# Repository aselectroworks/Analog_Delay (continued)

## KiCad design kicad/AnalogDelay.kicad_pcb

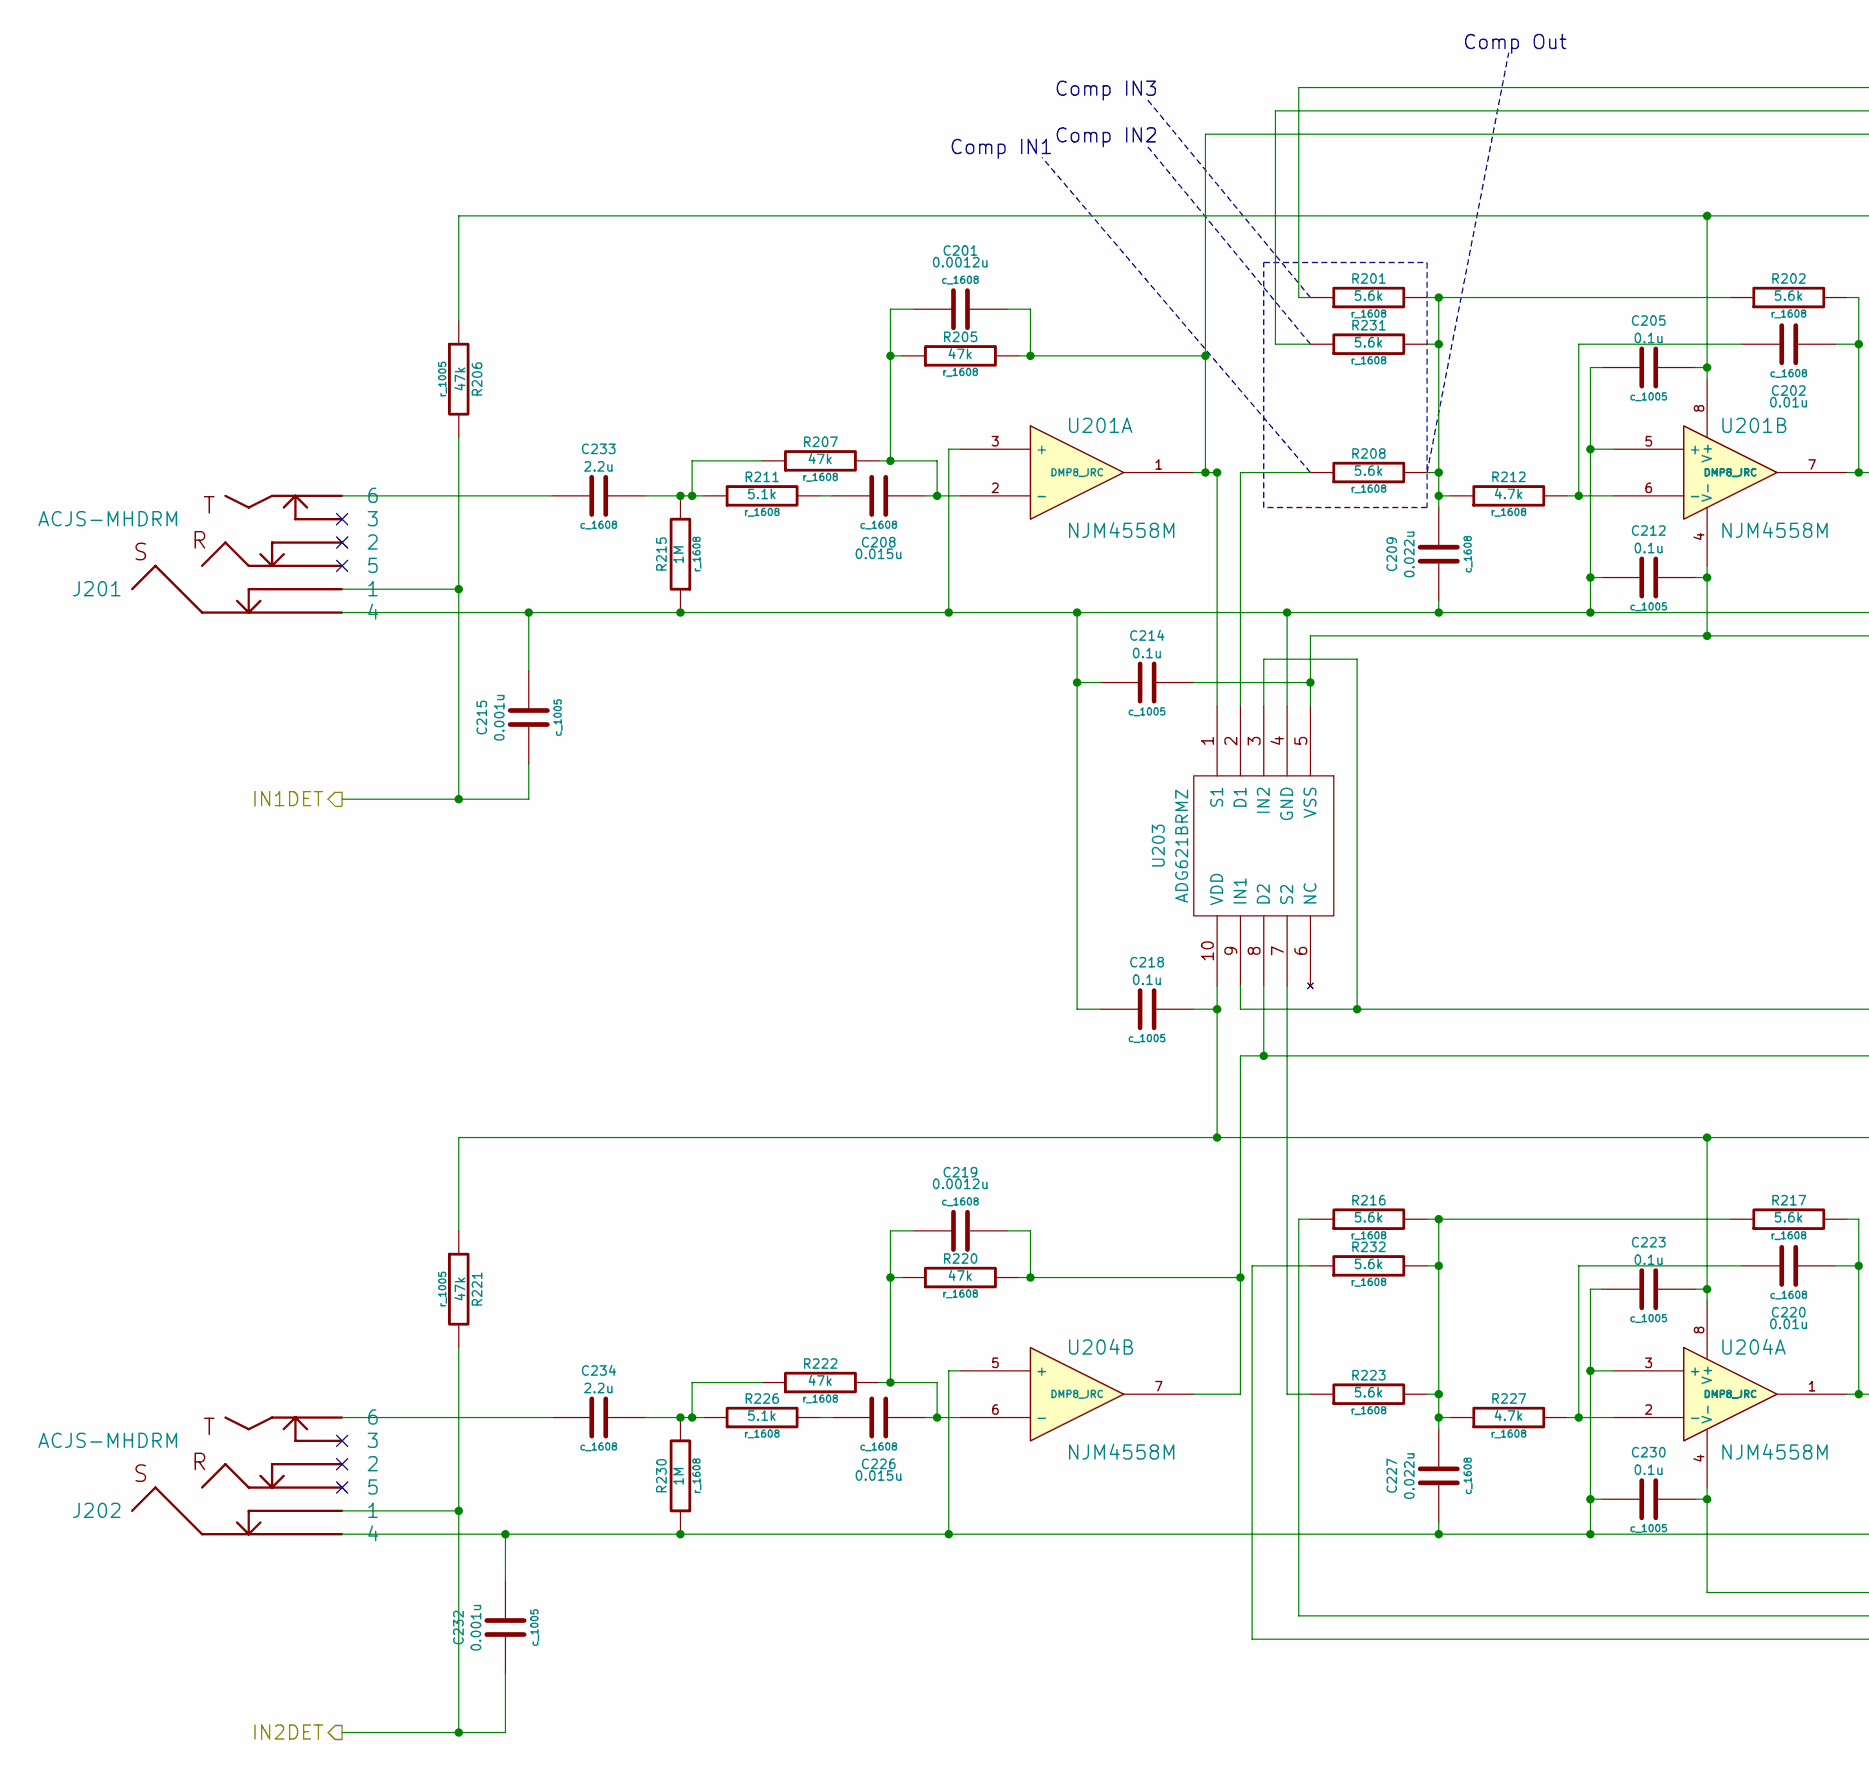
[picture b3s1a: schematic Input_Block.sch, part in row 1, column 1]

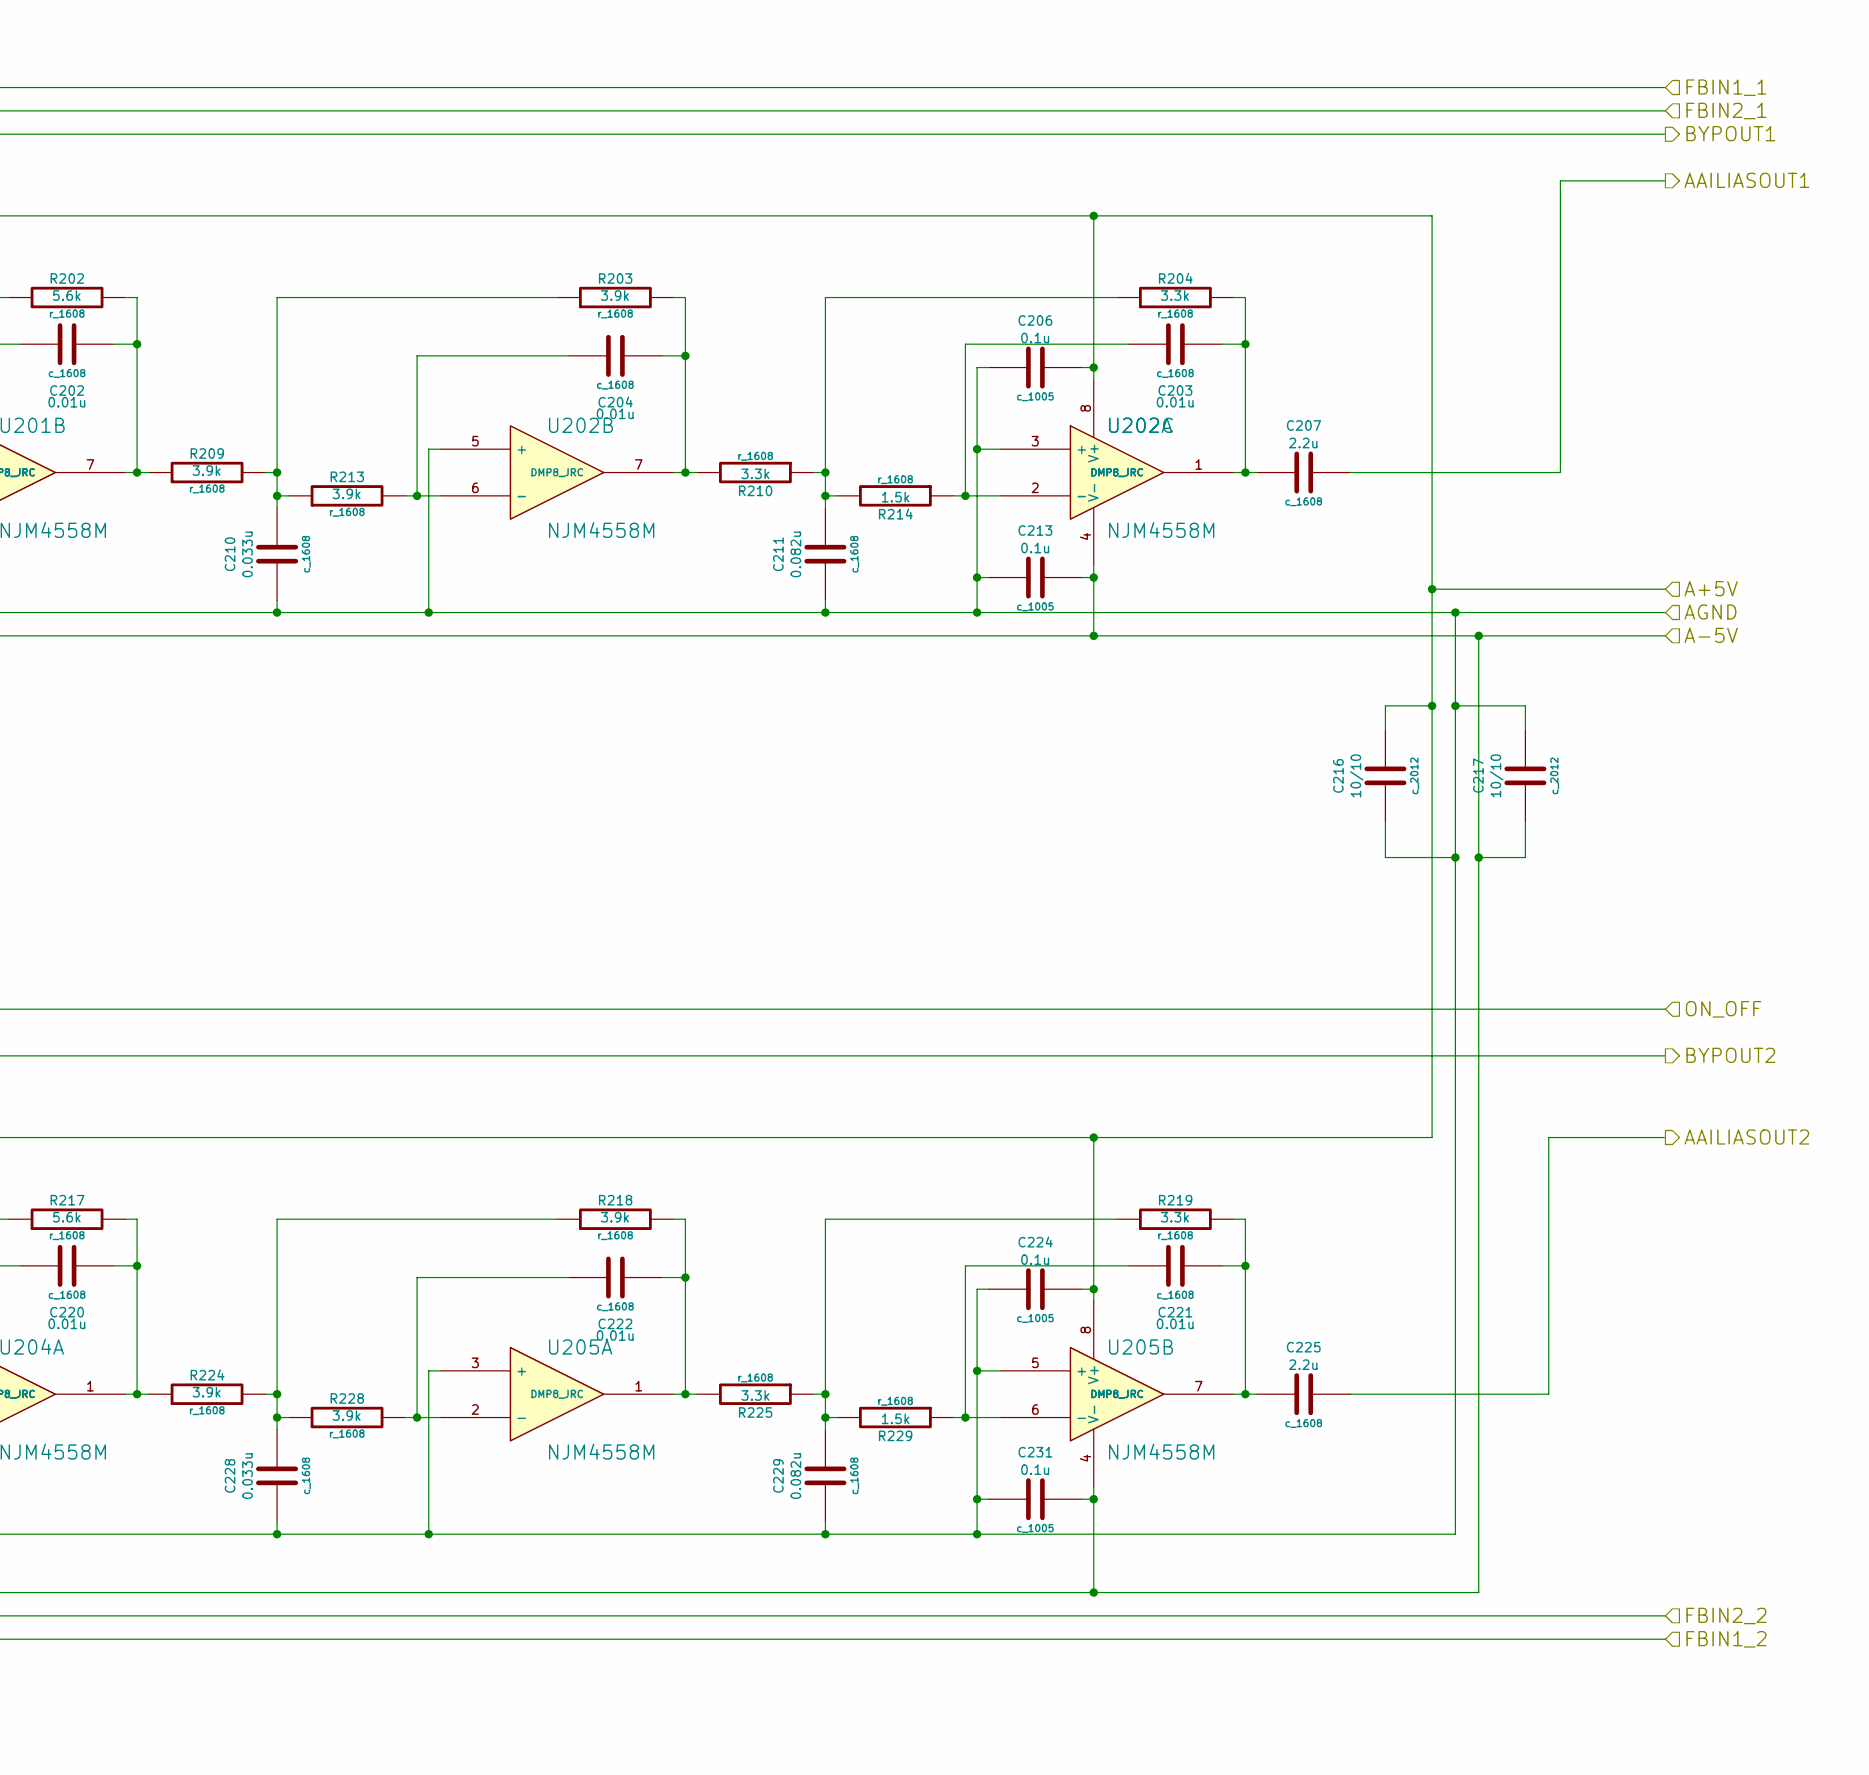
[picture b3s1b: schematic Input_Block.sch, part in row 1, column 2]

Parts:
C201, C219: 0.0012u; c_1608
C202, C203, C204, C220, C221, C222: 0.01u; c_1608
C205, C206, C212, C213, C214, C218, C223, C224, C230, C231: 0.1u; c_1005
C207, C225, C233, C234: 2.2u; c_1608
C208, C226: 0.015u; c_1608
C209, C227: 0.022u; c_1608
C210, C228: 0.033u; c_1608
C211, C229: 0.082u; c_1608
C215, C232: 0.001u; c_1005
C216, C217: 10/10; c_2012
J201, J202: ACJS-MHDRM
R201, R202, R208, R216, R217, R223, R231, R232: 5.6k; r_1608
R203, R209, R213, R218, R224, R228: 3.9k; r_1608
R204, R210, R219, R225: 3.3k; r_1608
R205, R207, R220, R222: 47k; r_1608
R206, R221: 47k; r_1005
R211, R226: 5.1k; r_1608
R212, R227: 4.7k; r_1608
R214, R229: 1.5k; r_1608
R215, R230: 1M; r_1608
U201, U202, U204, U205: NJM4558M; DMP8_JRC
U203: ADG621BRMZ; RM-10

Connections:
+5VA: C205.2, C206.2, C216.2, C218.2, C223.2, C224.2, R206.1, R221.1, U201.8 (V+), U202.8 (V+), U203.10 (VDD), U204.8 (V+), U205.8 (V+); also elsewhere on the board
-5VA: C212.2, C213.2, C214.2, C217.1, C230.2, C231.2, U201.4 (V-), U202.4 (V-), U203.5 (VSS), U204.4 (V-), U205.4 (V-); also elsewhere on the board
/Clock Cancel Filter/Output Block/BYP1IN: C201.1, R205.2, U201.1, U203.1 (S1); also elsewhere on the board
/Clock Cancel Filter/Output Block/BYPIN2: C219.1, R220.2, U203.8 (D2), U204.7; also elsewhere on the board
/Connect Block/ON_OFF: U203.3 (IN2), U203.9 (IN1); also elsewhere on the board
/Input/Anti Alias Filter Block/AAILIASOUT1: C207.2; also elsewhere on the board
/Input/Anti Alias Filter Block/AAILIASOUT2: C225.2; also elsewhere on the board
/Input/Anti Alias Filter Block/FBIN1_1: R201.1; also elsewhere on the board
/Input/Anti Alias Filter Block/FBIN1_2: R232.1; also elsewhere on the board
/Input/Anti Alias Filter Block/FBIN2_1: R231.1; also elsewhere on the board
/Input/Anti Alias Filter Block/FBIN2_2: R216.1; also elsewhere on the board
/Input/Anti Alias Filter Block/IN1DET: C215.1, J201.1, R206.2; also elsewhere on the board
/Input/Anti Alias Filter Block/IN2DET: C232.1, J202.1, R221.2; also elsewhere on the board
AGND: C205.1, C206.1, C209.1, C210.1, C211.1, C212.1, C213.1, C214.1, C215.2, C216.1, C217.2, C218.1, C223.1, C224.1, C227.1, C228.1, C229.1, C230.1, C231.1, C232.2, J201.4, J202.4, R215.1, R230.1, U201.3 (+), U201.5 (+), U202.3 (+), U202.5 (+), U203.4 (GND), U204.3 (+), U204.5 (+), U205.3 (+), U205.5 (+); also elsewhere on the board
unnamed: C220.2, R217.2, R224.1, U204.1
unnamed: C228.2, R218.1, R224.2, R228.1
unnamed: C221.1, R229.1, U205.6 (-)
unnamed: C220.1, R227.2, U204.2 (-)
unnamed: C229.2, R219.1, R225.1, R229.2
unnamed: C222.2, R218.2, R225.2, U205.1
unnamed: C222.1, R228.2, U205.2 (-)
unnamed: C211.2, R204.1, R210.1, R214.2
unnamed: C203.1, R214.1, U202.2 (-)
unnamed: C204.2, R203.2, R210.2, U202.7
unnamed: C226.1, R226.2
unnamed: C219.2, C226.2, R220.1, R222.2, U204.6 (-)
unnamed: C203.2, C207.1, R204.2, U202.1
unnamed: R208.1, U203.2 (D1)
unnamed: R223.1, U203.7 (S2)
unnamed: C227.2, R216.2, R217.1, R223.2, R227.1, R232.2
unnamed: C233.1, J201.6
unnamed: C234.1, J202.6
unnamed: C221.2, C225.1, R219.2, U205.7
unnamed: C210.2, R203.1, R209.2, R213.1
unnamed: C202.2, R202.2, R209.1, U201.7
unnamed: C209.2, R201.2, R202.1, R208.2, R212.1, R231.2
unnamed: C201.2, C208.2, R205.1, R207.2, U201.2 (-)
unnamed: C233.2, R207.1, R211.1, R215.2
unnamed: C208.1, R211.2
unnamed: C204.1, R213.2, U202.6 (-)
unnamed: C202.1, R212.2, U201.6 (-)
unnamed: C234.2, R222.1, R226.1, R230.2

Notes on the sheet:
Comp IN1
Comp IN2
Comp IN3
Comp Out

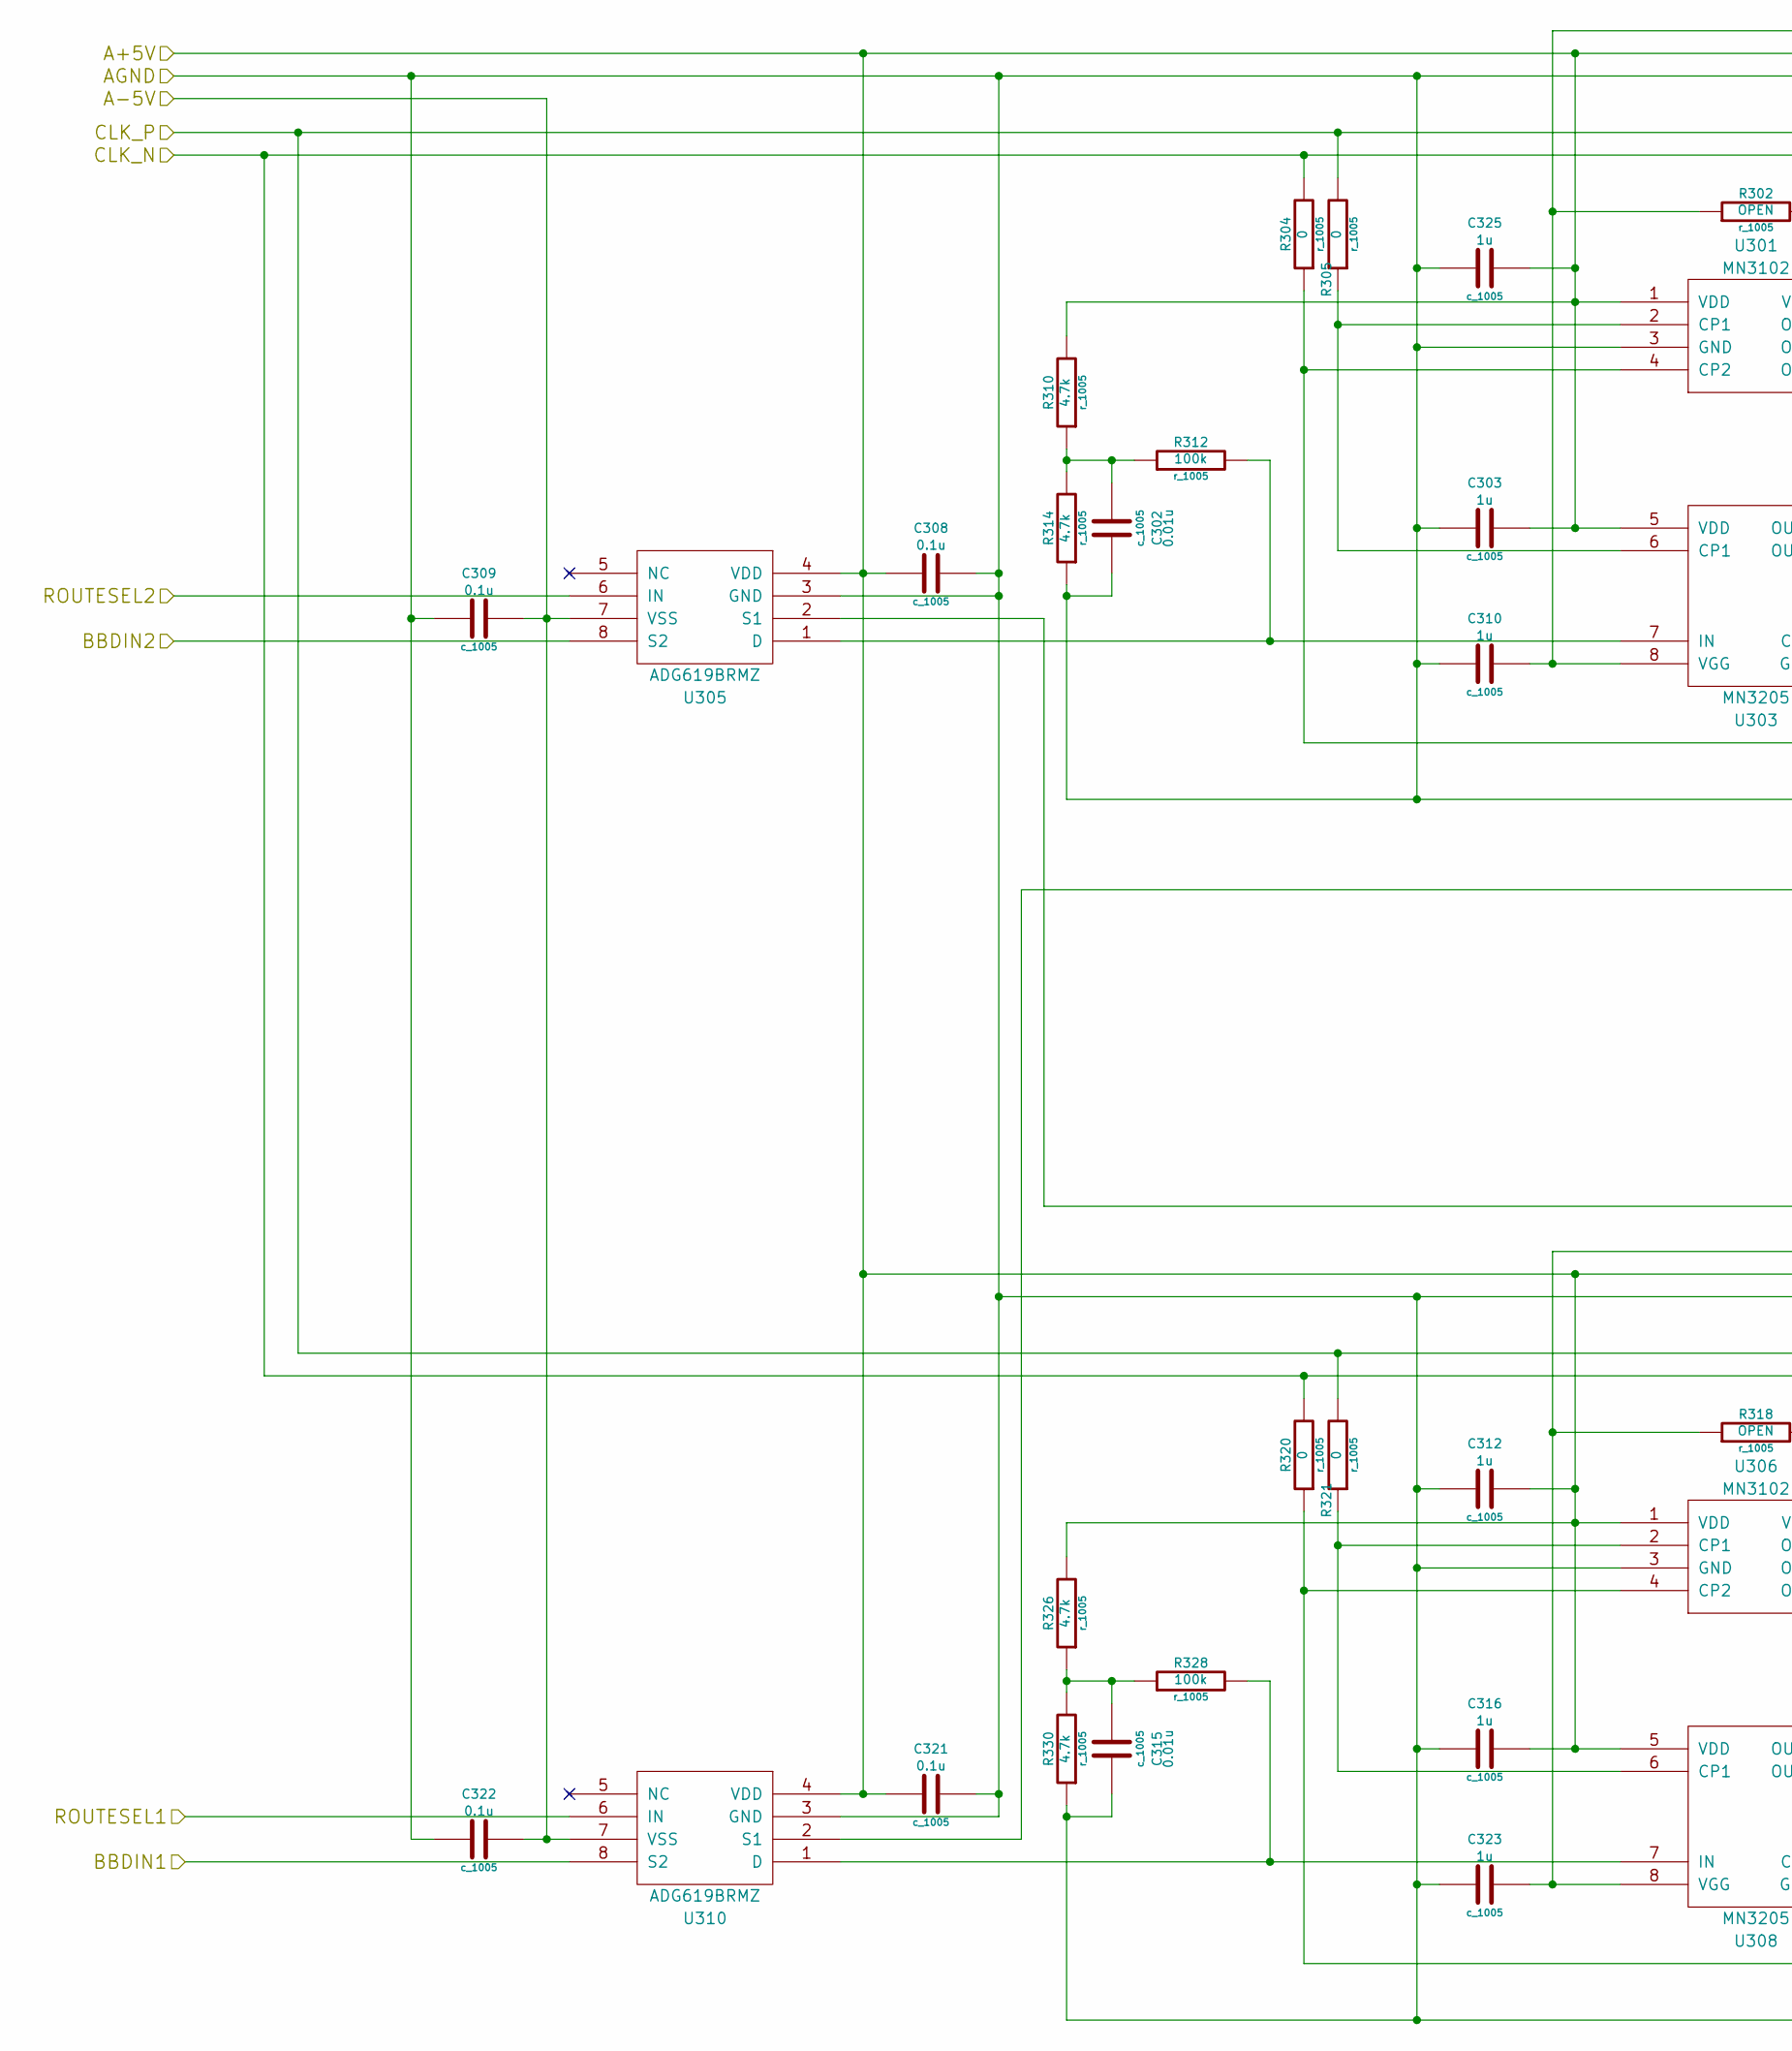
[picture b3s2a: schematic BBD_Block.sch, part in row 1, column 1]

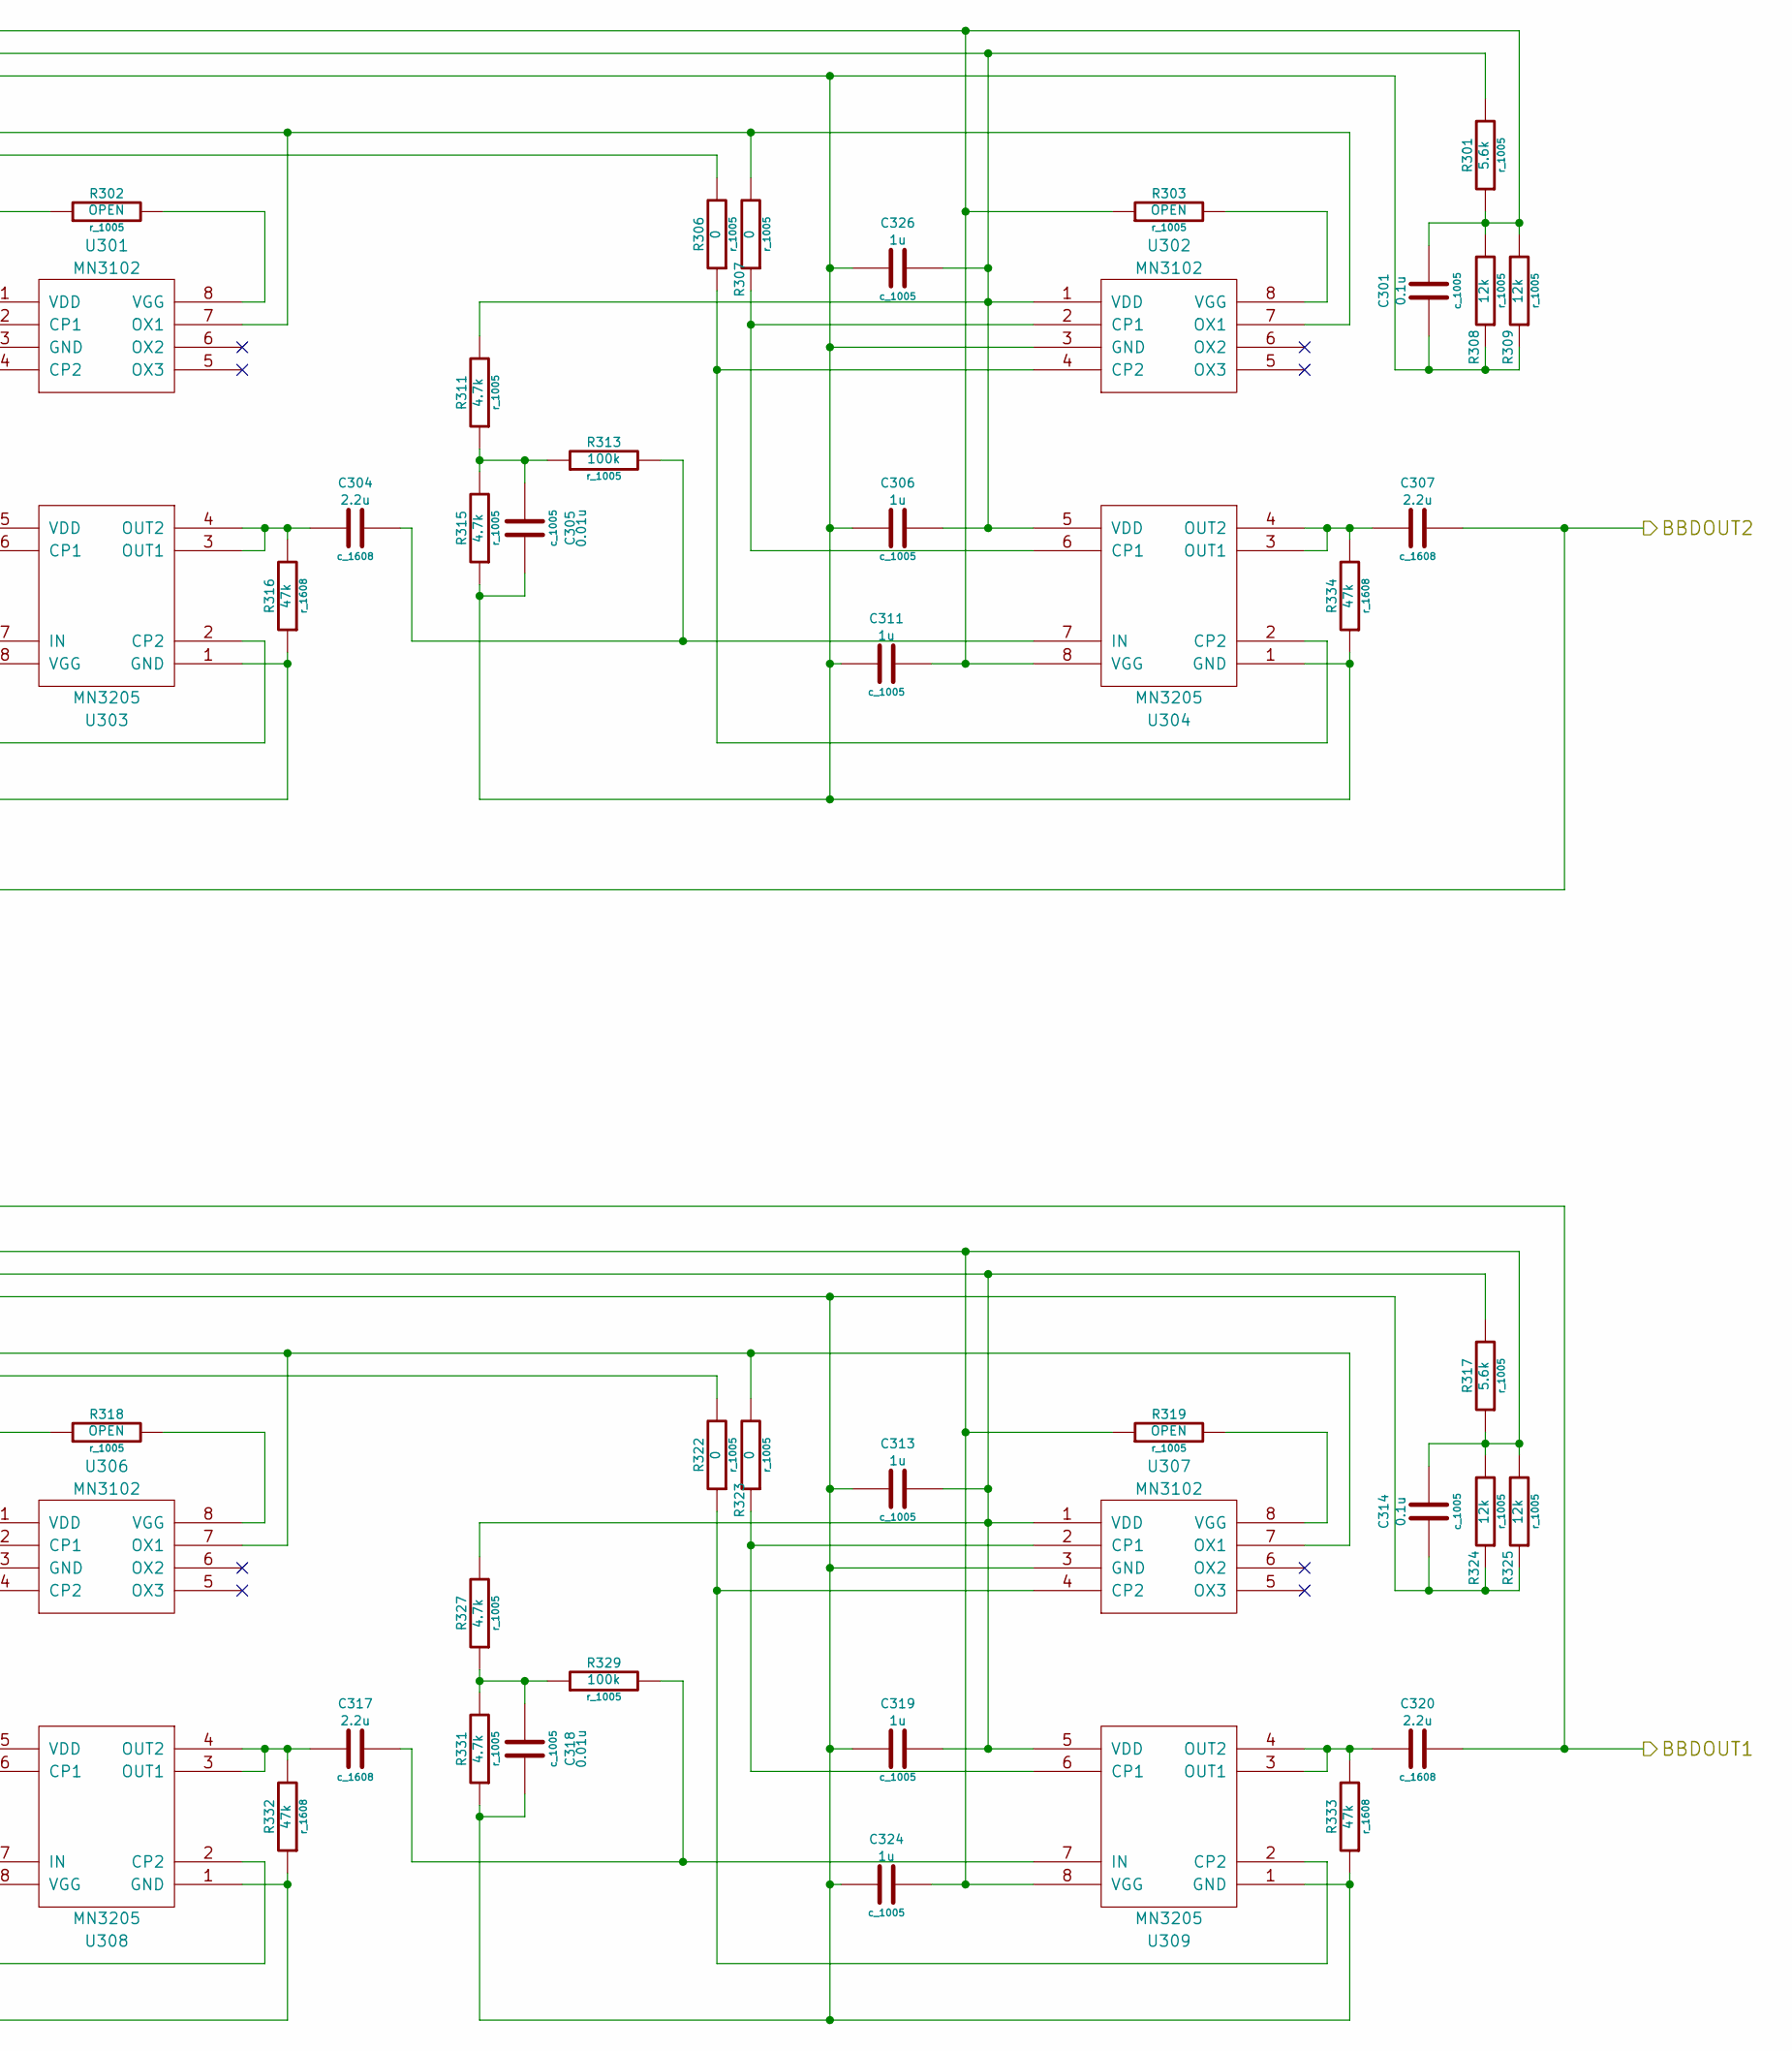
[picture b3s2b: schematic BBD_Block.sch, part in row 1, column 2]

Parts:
C301, C308, C309, C314, C321, C322: 0.1u; c_1005
C302, C305, C315, C318: 0.01u; c_1005
C303, C306, C310, C311, C312, C313, C316, C319, C323, C324, C325, C326: 1u; c_1005
C304, C307, C317, C320: 2.2u; c_1608
R301, R317: 5.6k; r_1005
R302, R303, R318, R319: OPEN; r_1005
R304, R305, R306, R307, R320, R321, R322, R323: 0; r_1005
R308, R309, R324, R325: 12k; r_1005
R310, R311, R314, R315, R326, R327, R330, R331: 4.7k; r_1005
R312, R313, R328, R329: 100k; r_1005
R316, R332, R333, R334: 47k; r_1608
U301, U302, U306, U307: MN3102
U303, U304, U308, U309: MN3205; DIP-14-6
U305, U310: ADG619BRMZ; RM-8

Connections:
+5VA: C303.2, C306.2, C308.1, C312.2, C313.2, C316.2, C319.2, C321.1, C325.2, C326.2, R301.2, R310.2, R311.2, R317.2, R326.2, R327.2, U301.1 (VDD), U302.1 (VDD), U303.5 (VDD), U304.5 (VDD), U305.4 (VDD), U306.1 (VDD), U307.1 (VDD), U308.5 (VDD), U309.5 (VDD), U310.4 (VDD); also elsewhere on the board
-5VA: C309.2, C322.2, U305.7 (VSS), U310.7 (VSS); also elsewhere on the board
/BBD Block/BBDOUT1: C320.2, U305.2 (S1); also elsewhere on the board
/BBD Block/BBDOUT2: C307.2, U310.2 (S1); also elsewhere on the board
/BBD Block/CLK_N: R304.2, R306.2, R320.2, R322.2; also elsewhere on the board
/BBD Block/CLK_P: R305.2, R307.2, R321.2, R323.2, U301.7 (OX1), U302.7 (OX1), U306.7 (OX1), U307.7 (OX1); also elsewhere on the board
/Input/Anti Alias Filter Block/AAILIASOUT1: U310.8 (S2); also elsewhere on the board
/Input/Anti Alias Filter Block/AAILIASOUT2: U305.8 (S2); also elsewhere on the board
/Input/Anti Alias Filter Block/IN1DET: U310.6 (IN); also elsewhere on the board
/Input/Anti Alias Filter Block/IN2DET: U305.6 (IN); also elsewhere on the board
AGND: C301.1, C302.1, C303.1, C305.1, C306.1, C308.2, C309.1, C310.1, C311.1, C312.1, C313.1, C314.1, C315.1, C316.1, C318.1, C319.1, C321.2, C322.1, C323.1, C324.1, C325.1, C326.1, R308.1, R309.1, R314.1, R315.1, R316.1, R324.1, R325.1, R330.1, R331.1, R332.1, R333.1, R334.1, U301.3 (GND), U302.3 (GND), U303.1 (GND), U304.1 (GND), U305.3 (GND), U306.3 (GND), U307.3 (GND), U308.1 (GND), U309.1 (GND), U310.3 (GND); also elsewhere on the board
unnamed: C317.1, R332.2, U308.3 (OUT1), U308.4 (OUT2)
unnamed: R305.1, U301.2 (CP1), U303.6 (CP1)
unnamed: R321.1, U306.2 (CP1), U308.6 (CP1)
unnamed: C315.2, R326.1, R328.1, R330.2
unnamed: R320.1, U306.4 (CP2), U308.2 (CP2)
unnamed: R318.2, U306.8 (VGG)
unnamed: R304.1, U301.4 (CP2), U303.2 (CP2)
unnamed: C302.2, R310.1, R312.1, R314.2
unnamed: R312.2, U303.7 (IN), U305.1 (D)
unnamed: C305.2, R311.1, R313.1, R315.2
unnamed: R307.1, U302.2 (CP1), U304.6 (CP1)
unnamed: R306.1, U302.4 (CP2), U304.2 (CP2)
unnamed: C304.2, R313.2, U304.7 (IN)
unnamed: C307.1, R334.2, U304.3 (OUT1), U304.4 (OUT2)
unnamed: R319.2, U307.8 (VGG)
unnamed: C318.2, R327.1, R329.1, R331.2
unnamed: C317.2, R329.2, U309.7 (IN)
unnamed: R323.1, U307.2 (CP1), U309.6 (CP1)
unnamed: R322.1, U307.4 (CP2), U309.2 (CP2)
unnamed: C304.1, R316.2, U303.3 (OUT1), U303.4 (OUT2)
unnamed: C320.1, R333.2, U309.3 (OUT1), U309.4 (OUT2)
unnamed: C314.2, C323.2, C324.2, R317.1, R318.1, R319.1, R324.2, R325.2, U308.8 (VGG), U309.8 (VGG)
unnamed: R302.2, U301.8 (VGG)
unnamed: R328.2, U308.7 (IN), U310.1 (D)
unnamed: R303.2, U302.8 (VGG)
unnamed: C301.2, C310.2, C311.2, R301.1, R302.1, R303.1, R308.2, R309.2, U303.8 (VGG), U304.8 (VGG)

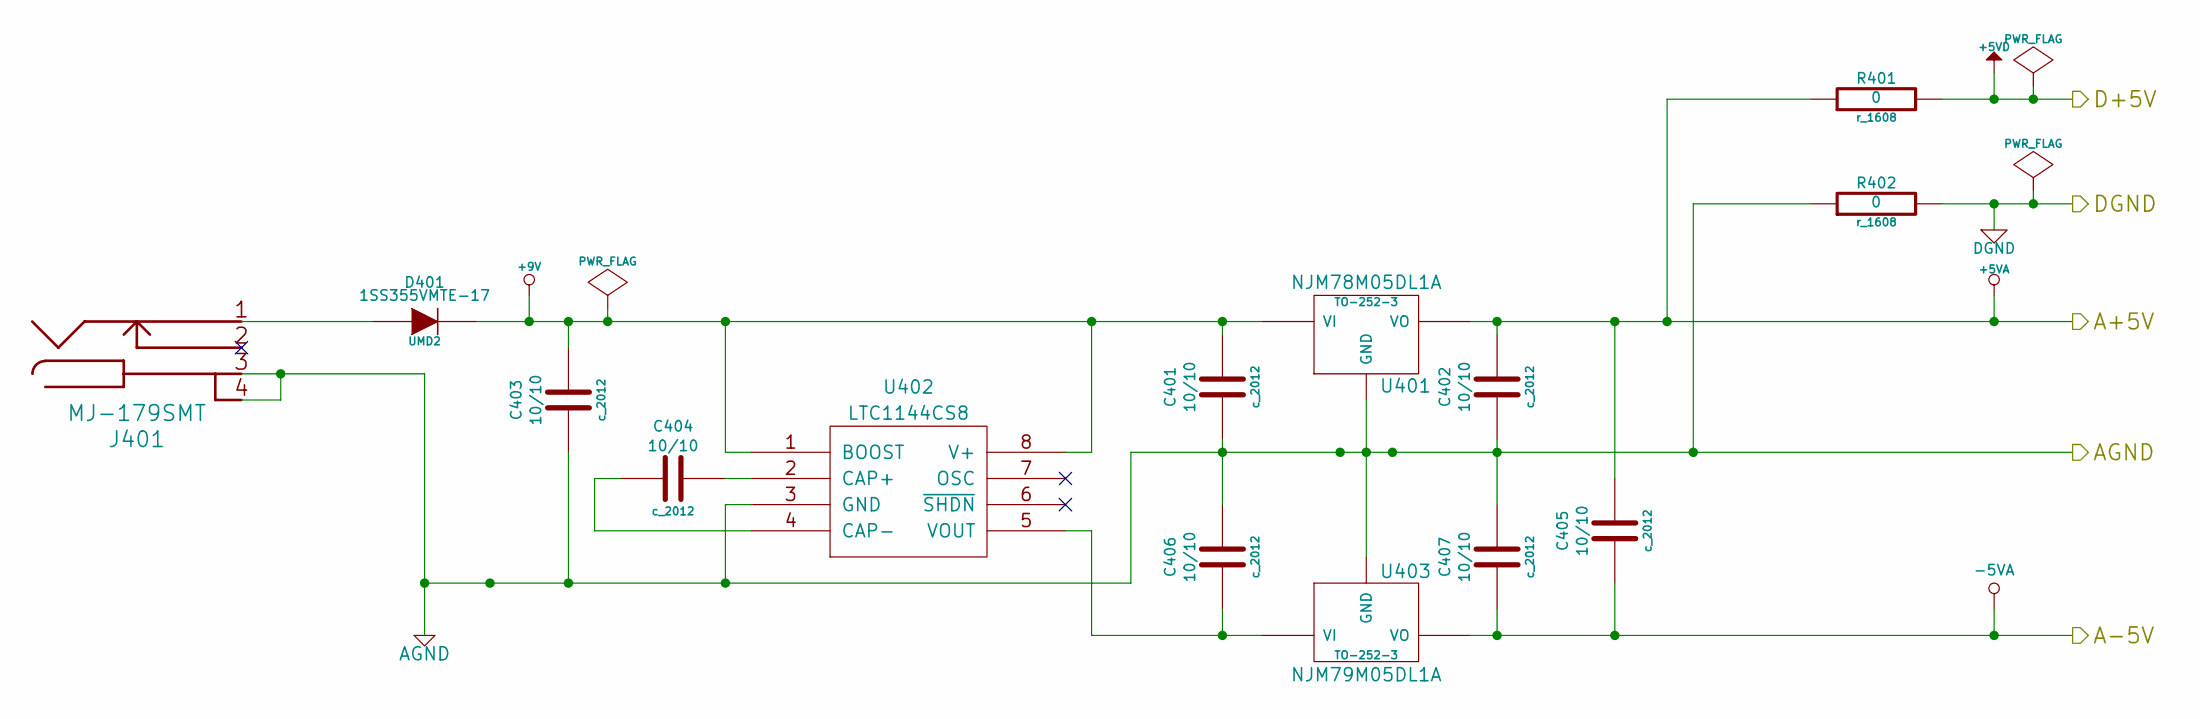
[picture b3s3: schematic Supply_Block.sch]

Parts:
C401, C402, C403, C404, C405, C406, C407: 10/10; c_2012
D401: 1SS355VMTE-17; UMD2
J401: MJ-179SMT
R401, R402: 0; r_1608
U401: NJM78M05DL1A; TO-252-3
U402: LTC1144CS8; S8_LT
U403: NJM79M05DL1A; TO-252-3

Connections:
+5VA: C402.2, C405.2, R401.1, U401.3 (VO); also elsewhere on the board
+5VD: R401.2; also elsewhere on the board
+9V: C401.2, C403.2, D401.2 (K), U401.1 (VI), U402.1 (BOOST), U402.8 (V+)
-5VA: C405.1, C407.1, U403.3 (VO); also elsewhere on the board
AGND: C401.1, C402.1, C403.1, C406.2, C407.2, J401.3, J401.4, R402.1, U401.2 (GND), U402.3 (GND), U403.1 (GND); also elsewhere on the board
DGND: R402.2; also elsewhere on the board
unnamed: C406.1, U402.5 (VOUT), U403.2 (VI)
unnamed: D401.1 (A), J401.1
unnamed: C404.1, U402.4 (CAP-)
unnamed: C404.2, U402.2 (CAP+)
